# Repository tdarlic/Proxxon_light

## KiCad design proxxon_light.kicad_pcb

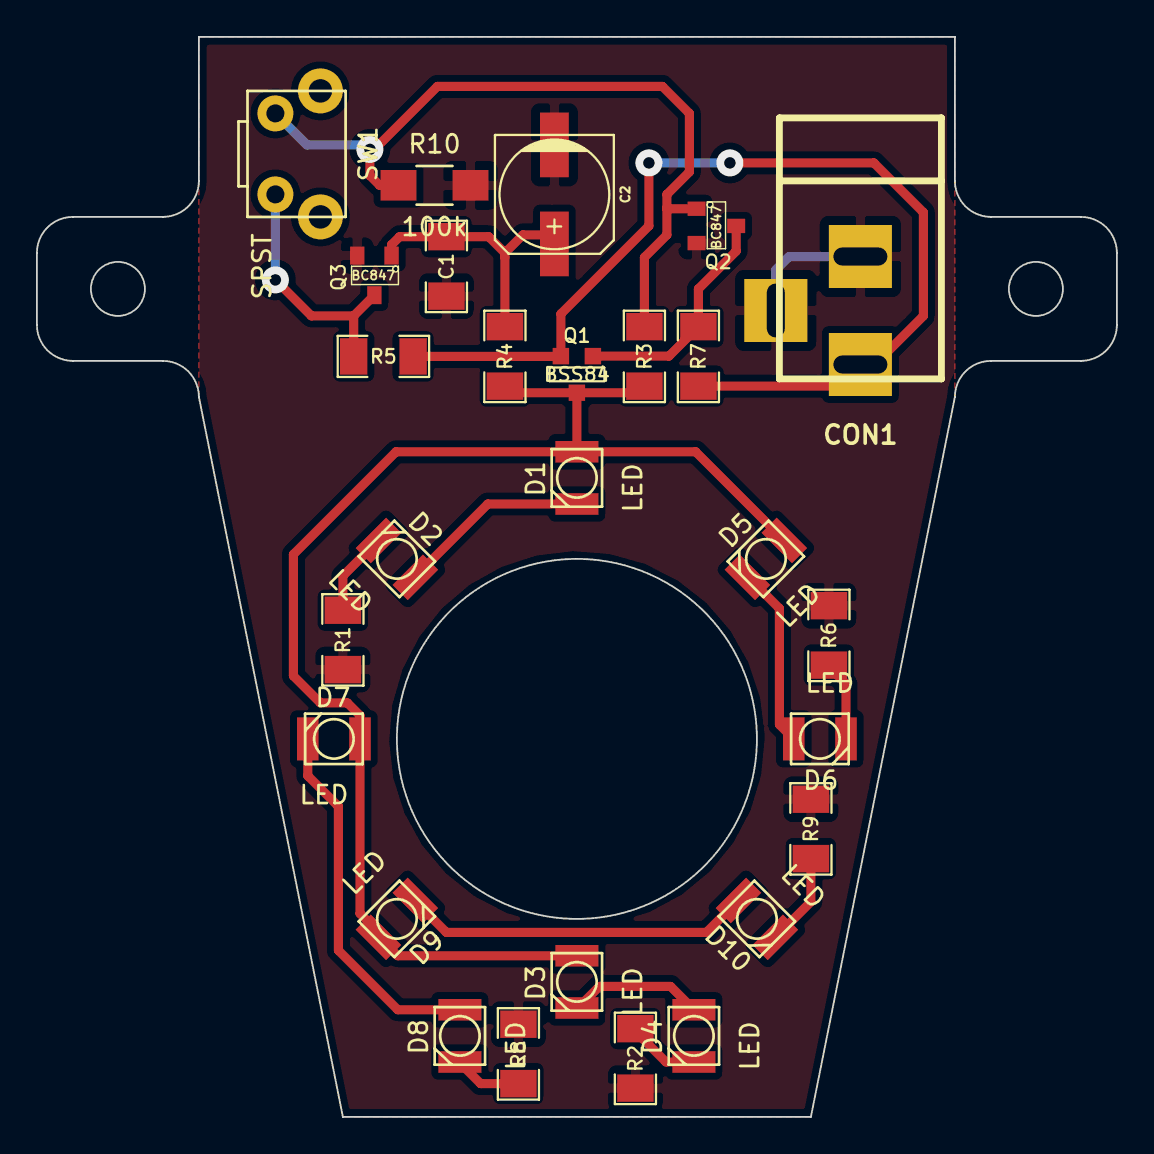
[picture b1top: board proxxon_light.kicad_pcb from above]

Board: 2 copper layers, 60.0 x 60.0 mm, 27 parts (0 on the bottom side), 17 nets.

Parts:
C1: 22u; SM1206
C2: 22u; c_elec_6.3x5.3
CON1: BARREL_JACK
D1, D2, D3, D4, D5, D6, D7, D8, D9, D10: LED; LED_2437
Q1: BSS84; SOT23GDS
Q2, Q3: BC847; SOT23
R1, R2, R6, R8, R9: 150R; SM1206
R3, R5, R7: 100k; SM1206
R4: 1M; SM1206
R10: 100k; R_1206_HandSoldering
SW1: SPST; MICRO_PUSH_SWITCH

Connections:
GND: C1.2, C2.2, CON1.2, CON1.3, Q2.2, Q3.2, R1.2, R2.2, R6.2, R8.2, R9.2, R10.2
unnamed: C1.1, C2.1, Q3.1, R4.2
unnamed: D1.1, D3.1, D5.1, D7.1, D9.1, Q1.D, R3.1, R4.1
unnamed: D1.2, D2.1
unnamed: D2.2, R1.1
unnamed: D3.2, D4.1
unnamed: D4.2, R2.1
unnamed: D5.2, D6.1
unnamed: D6.2, R6.1
unnamed: D7.2, D8.1
unnamed: D8.2, R8.1
unnamed: D9.2, D10.1
unnamed: D10.2, R9.1
unnamed: Q1.G, Q2.3, R7.2
unnamed: Q2.1, R3.2, R10.1, SW1.1
unnamed: Q3.3, R5.2, SW1.2
VCC: CON1.1, Q1.S, R5.1, R7.1

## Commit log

2015-01-07 :space_invader: Added .gitattributes & .gitignore files
